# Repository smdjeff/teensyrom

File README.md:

# teensy rom

* Plugs directly into a 2716/512 socket
* Runs very fast firmware to emulate an 2716/512 EEPROM
* Loads rom.bin from SD card
* Polls CS pin to toggle data output or tristate
* Up to 64KB supported with jumpers to a board beyond the 2716 socket

## Dependencies
* https://www.adafruit.com/product/4622
* Arduino IDE
* Teensy 4.1
* Jumper wires
* $10 level shifting PCBA from JLCPCB (fabrication outputs included)

## Inspired
by Ted Fried, MicroCore Labs [ROM Emulator](https://github.com/MicroCoreLabs/Projects/tree/master/EPROM_Emulator)

2716             |  27512
:-------------------------:|:-------------------------:
  |

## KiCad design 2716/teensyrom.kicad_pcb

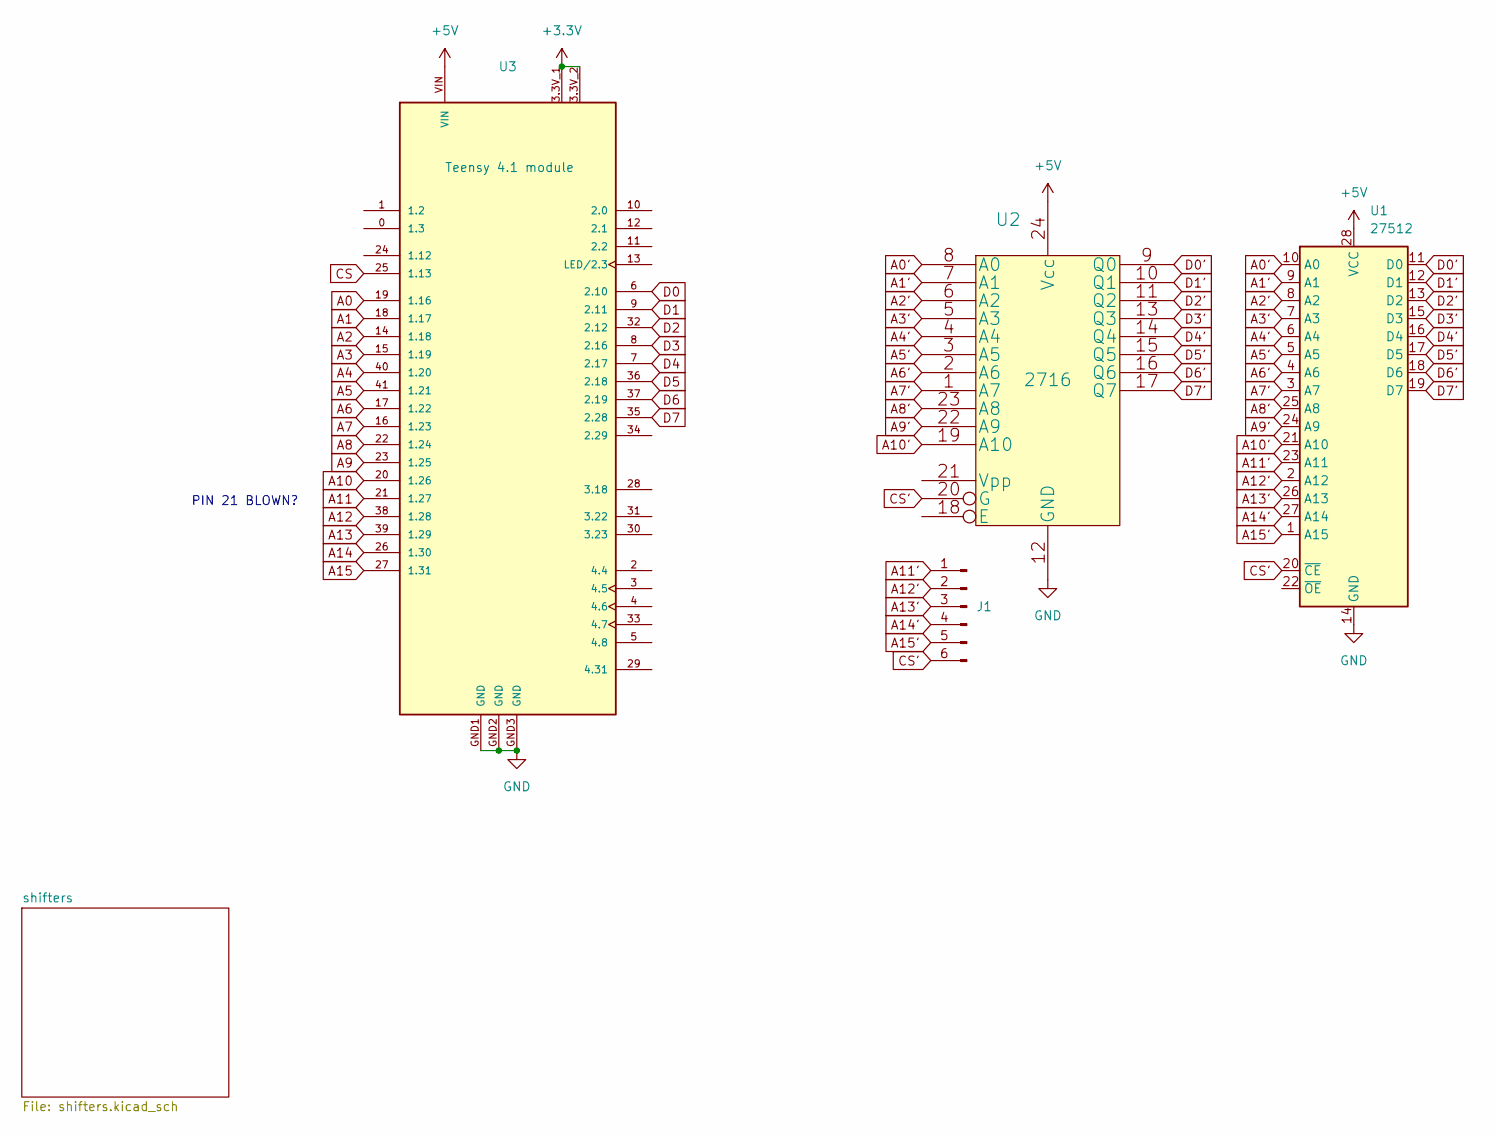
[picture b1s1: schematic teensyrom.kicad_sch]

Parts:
J1: Conn_01x06_Pin; PinHeader_1x06_P2.54mm_Vertical
U1: 27512; DIP-28_W15.24mm
U2: 2716; DIP-24_W15.24mm
U3: Teensy 4.1 module; MODULE_DEV-16771; PARTREV 4.1

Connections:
+3.3V: U3.3.3V_1, U3.3.3V_2; also elsewhere on the board
+5V: U1.28 (VCC), U2.24 (Vcc), U3.VIN; also elsewhere on the board
A0: U3.19 (1.16); also elsewhere on the board
A0': U1.10 (A0), U2.8 (A0); also elsewhere on the board
A1: U3.18 (1.17); also elsewhere on the board
A1': U1.9 (A1), U2.7 (A1); also elsewhere on the board
A2: U3.14 (1.18); also elsewhere on the board
A2': U1.8 (A2), U2.6 (A2); also elsewhere on the board
A3: U3.15 (1.19); also elsewhere on the board
A3': U1.7 (A3), U2.5 (A3); also elsewhere on the board
A4: U3.40 (1.20); also elsewhere on the board
A4': U1.6 (A4), U2.4 (A4); also elsewhere on the board
A5: U3.41 (1.21); also elsewhere on the board
A5': U1.5 (A5), U2.3 (A5); also elsewhere on the board
A6: U3.17 (1.22); also elsewhere on the board
A6': U1.4 (A6), U2.2 (A6); also elsewhere on the board
A7: U3.16 (1.23); also elsewhere on the board
A7': U1.3 (A7), U2.1 (A7); also elsewhere on the board
A8: U3.22 (1.24); also elsewhere on the board
A8': U1.25 (A8), U2.23 (A8); also elsewhere on the board
A9: U3.23 (1.25); also elsewhere on the board
A9': U1.24 (A9), U2.22 (A9); also elsewhere on the board
A10: U3.20 (1.26); also elsewhere on the board
A10': U1.21 (A10), U2.19 (A10); also elsewhere on the board
A11: U3.21 (1.27); also elsewhere on the board
A11': J1.1, U1.23 (A11); also elsewhere on the board
A12: U3.38 (1.28); also elsewhere on the board
A12': J1.2, U1.2 (A12); also elsewhere on the board
A13: U3.39 (1.29); also elsewhere on the board
A13': J1.3, U1.26 (A13); also elsewhere on the board
A14: U3.26 (1.30); also elsewhere on the board
A14': J1.4, U1.27 (A14); also elsewhere on the board
A15: U3.27 (1.31); also elsewhere on the board
A15': J1.5, U1.1 (A15); also elsewhere on the board
CS: U3.25 (1.13); also elsewhere on the board
CS': J1.6, U1.20 (~CE), U2.20 (G); also elsewhere on the board
D0: U3.6 (2.10); also elsewhere on the board
D0': U1.11 (D0), U2.9 (Q0); also elsewhere on the board
D1: U3.9 (2.11); also elsewhere on the board
D1': U1.12 (D1), U2.10 (Q1); also elsewhere on the board
D2: U3.32 (2.12); also elsewhere on the board
D2': U1.13 (D2), U2.11 (Q2); also elsewhere on the board
D3: U3.8 (2.16); also elsewhere on the board
D3': U1.15 (D3), U2.13 (Q3); also elsewhere on the board
D4: U3.7 (2.17); also elsewhere on the board
D4': U1.16 (D4), U2.14 (Q4); also elsewhere on the board
D5: U3.36 (2.18); also elsewhere on the board
D5': U1.17 (D5), U2.15 (Q5); also elsewhere on the board
D6: U3.37 (2.19); also elsewhere on the board
D6': U1.18 (D6), U2.16 (Q6); also elsewhere on the board
D7: U3.35 (2.28); also elsewhere on the board
D7': U1.19 (D7), U2.17 (Q7); also elsewhere on the board
GND: U1.14 (GND), U2.12 (GND), U3.GND1 (GND), U3.GND2 (GND), U3.GND3 (GND)

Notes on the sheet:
PIN 21 BLOWN?

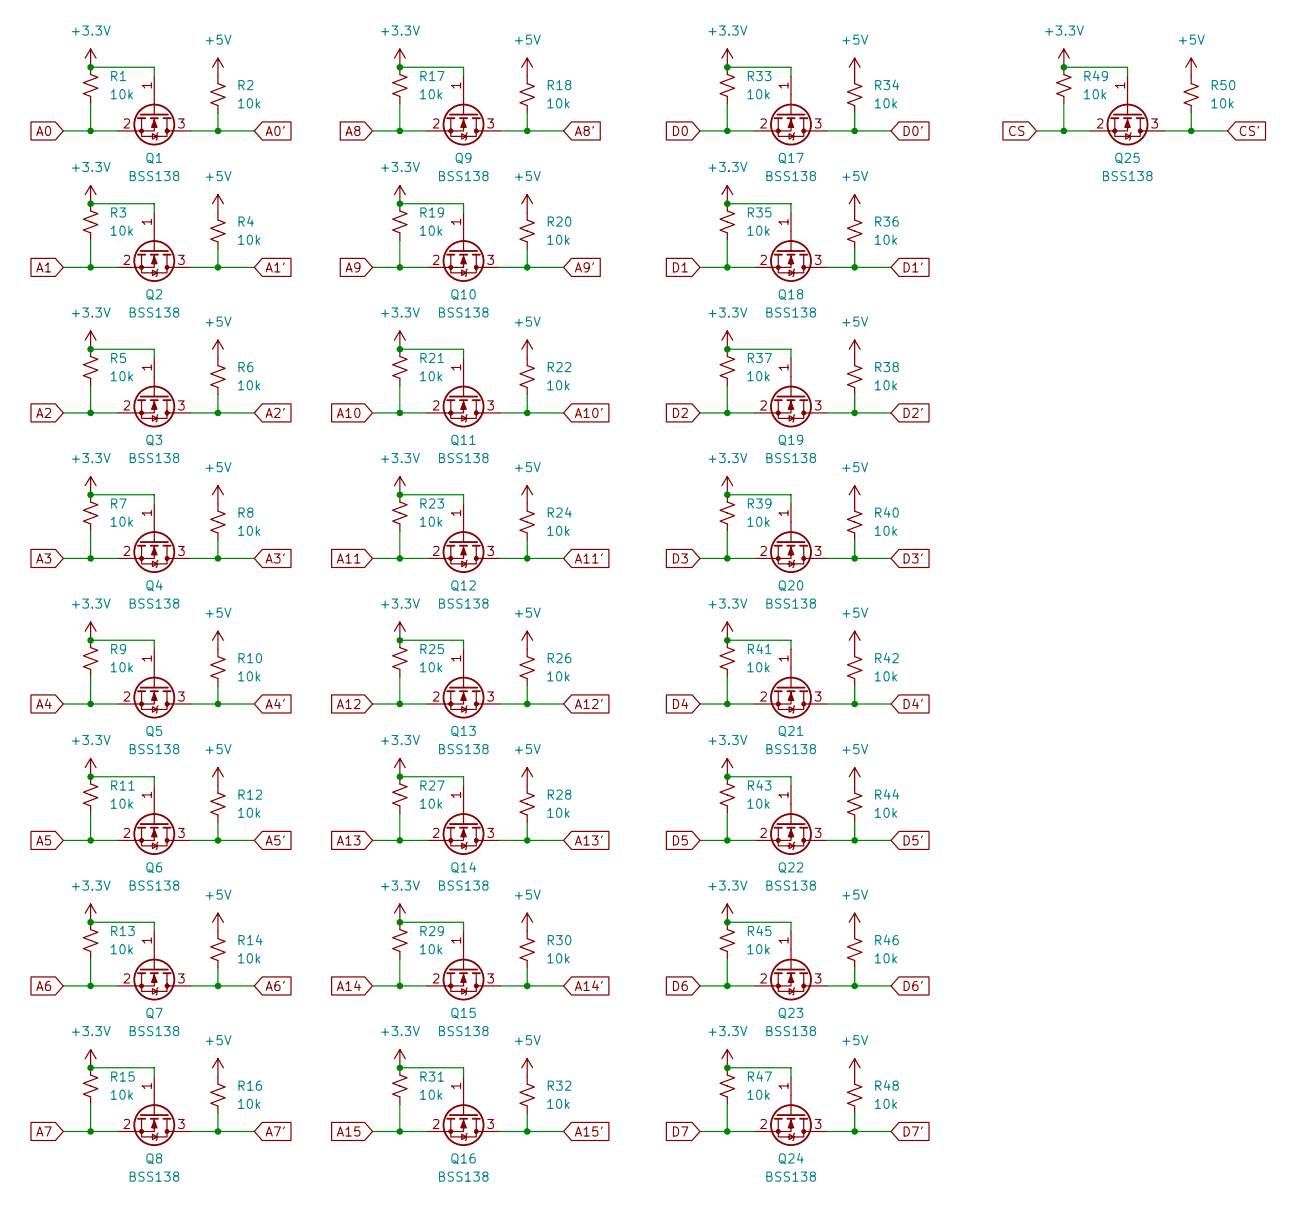
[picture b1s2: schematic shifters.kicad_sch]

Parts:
Q1, Q2, Q3, Q4, Q5, Q6, Q7, Q8, Q9, Q10, Q11, Q12, Q13, Q14, Q15, Q16, Q17, Q18, Q19, Q20, Q21, Q22, Q23, Q24, Q25: BSS138; SOT-23
R1, R2, R3, R4, R5, R6, R7, R8, R9, R10, R11, R12, R13, R14, R15, R16, R17, R18, R19, R20, R21, R22, R23, R24, R25, R26, R27, R28, R29, R30, R31, R32, R33, R34, R35, R36, R37, R38, R39, R40, R41, R42, R43, R44, R45, R46, R47, R48, R49, R50: 10k; R_0402_1005Metric

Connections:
+3.3V: Q1.1 (G), Q2.1 (G), Q3.1 (G), Q4.1 (G), Q5.1 (G), Q6.1 (G), Q7.1 (G), Q8.1 (G), Q9.1 (G), Q10.1 (G), Q11.1 (G), Q12.1 (G), Q13.1 (G), Q14.1 (G), Q15.1 (G), Q16.1 (G), Q17.1 (G), Q18.1 (G), Q19.1 (G), Q20.1 (G), Q21.1 (G), Q22.1 (G), Q23.1 (G), Q24.1 (G), Q25.1 (G), R1.1, R3.1, R5.1, R7.1, R9.1, R11.1, R13.1, R15.1, R17.1, R19.1, R21.1, R23.1, R25.1, R27.1, R29.1, R31.1, R33.1, R35.1, R37.1, R39.1, R41.1, R43.1, R45.1, R47.1, R49.1; also elsewhere on the board
+5V: R2.1, R4.1, R6.1, R8.1, R10.1, R12.1, R14.1, R16.1, R18.1, R20.1, R22.1, R24.1, R26.1, R28.1, R30.1, R32.1, R34.1, R36.1, R38.1, R40.1, R42.1, R44.1, R46.1, R48.1, R50.1; also elsewhere on the board
A0: Q1.2 (S), R1.2; also elsewhere on the board
A0': Q1.3 (D), R2.2; also elsewhere on the board
A1: Q2.2 (S), R3.2; also elsewhere on the board
A1': Q2.3 (D), R4.2; also elsewhere on the board
A2: Q3.2 (S), R5.2; also elsewhere on the board
A2': Q3.3 (D), R6.2; also elsewhere on the board
A3: Q4.2 (S), R7.2; also elsewhere on the board
A3': Q4.3 (D), R8.2; also elsewhere on the board
A4: Q5.2 (S), R9.2; also elsewhere on the board
A4': Q5.3 (D), R10.2; also elsewhere on the board
A5: Q6.2 (S), R11.2; also elsewhere on the board
A5': Q6.3 (D), R12.2; also elsewhere on the board
A6: Q7.2 (S), R13.2; also elsewhere on the board
A6': Q7.3 (D), R14.2; also elsewhere on the board
A7: Q8.2 (S), R15.2; also elsewhere on the board
A7': Q8.3 (D), R16.2; also elsewhere on the board
A8: Q9.2 (S), R17.2; also elsewhere on the board
A8': Q9.3 (D), R18.2; also elsewhere on the board
A9: Q10.2 (S), R19.2; also elsewhere on the board
A9': Q10.3 (D), R20.2; also elsewhere on the board
A10: Q11.2 (S), R21.2; also elsewhere on the board
A10': Q11.3 (D), R22.2; also elsewhere on the board
A11: Q12.2 (S), R23.2; also elsewhere on the board
A11': Q12.3 (D), R24.2; also elsewhere on the board
A12: Q13.2 (S), R25.2; also elsewhere on the board
A12': Q13.3 (D), R26.2; also elsewhere on the board
A13: Q14.2 (S), R27.2; also elsewhere on the board
A13': Q14.3 (D), R28.2; also elsewhere on the board
A14: Q15.2 (S), R29.2; also elsewhere on the board
A14': Q15.3 (D), R30.2; also elsewhere on the board
A15: Q16.2 (S), R31.2; also elsewhere on the board
A15': Q16.3 (D), R32.2; also elsewhere on the board
CS: Q25.2 (S), R49.2; also elsewhere on the board
CS': Q25.3 (D), R50.2; also elsewhere on the board
D0: Q17.2 (S), R33.2; also elsewhere on the board
D0': Q17.3 (D), R34.2; also elsewhere on the board
D1: Q18.2 (S), R35.2; also elsewhere on the board
D1': Q18.3 (D), R36.2; also elsewhere on the board
D2: Q19.2 (S), R37.2; also elsewhere on the board
D2': Q19.3 (D), R38.2; also elsewhere on the board
D3: Q20.2 (S), R39.2; also elsewhere on the board
D3': Q20.3 (D), R40.2; also elsewhere on the board
D4: Q21.2 (S), R41.2; also elsewhere on the board
D4': Q21.3 (D), R42.2; also elsewhere on the board
D5: Q22.2 (S), R43.2; also elsewhere on the board
D5': Q22.3 (D), R44.2; also elsewhere on the board
D6: Q23.2 (S), R45.2; also elsewhere on the board
D6': Q23.3 (D), R46.2; also elsewhere on the board
D7: Q24.2 (S), R47.2; also elsewhere on the board
D7': Q24.3 (D), R48.2; also elsewhere on the board

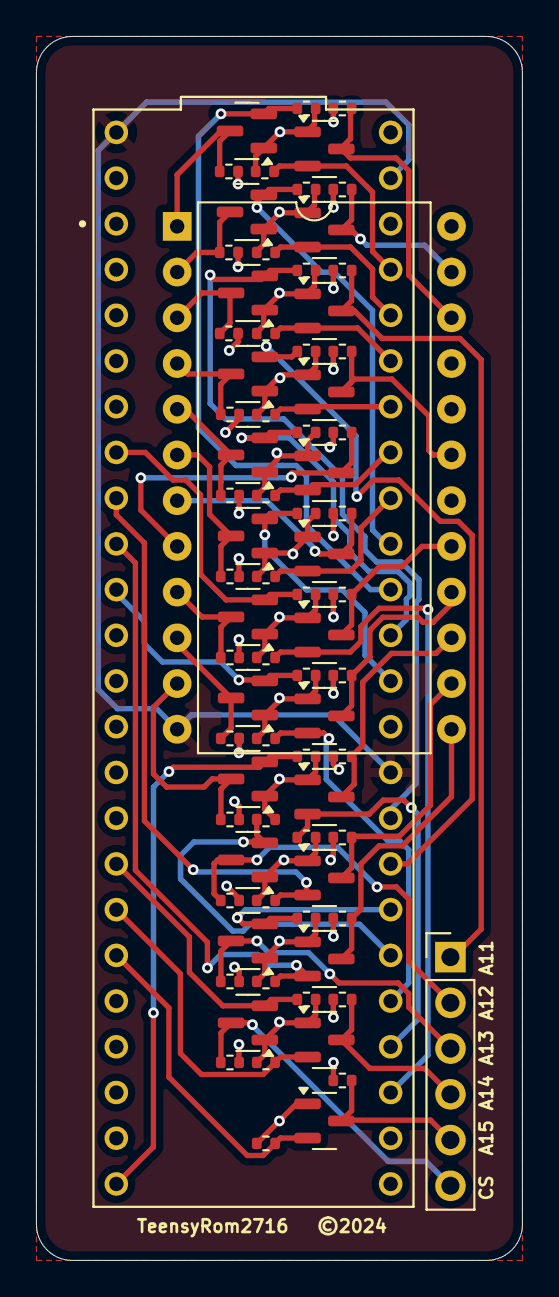
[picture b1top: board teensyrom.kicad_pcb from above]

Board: 4 copper layers, 27.0 x 68.0 mm, 78 parts (0 on the bottom side), 53 nets.

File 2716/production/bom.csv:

Designator,Footprint,Quantity,Value,LCSC Part #
"Q1, Q10, Q11, Q12, Q13, Q14, Q15, Q16, Q17, Q18, Q19, Q2, Q20, Q21, Q22, Q23, Q24, Q25, Q3, Q4, Q5, Q6, Q7, Q8, Q9",SOT-23,25,BSS138,
"R1, R10, R11, R12, R13, R14, R15, R16, R17, R18, R19, R2, R20, R21, R22, R23, R24, R25, R26, R27, R28, R29, R3, R30, R31, R32, R33, R34, R35, R36, R37, R38, R39, R4, R40, R41, R42, R43, R44, R45, R46, R47, R48, R49, R5, R50, R6, R7, R8, R9",0402,50,10k,
U2,DIP-24_W15.24mm,1,2716,
U3,MODULE_DEV-16771,1,Teensy 4.1 module,

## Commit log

2024-11-19 27512 version
2024-11-19 no message
2024-11-20 update schematic pdfs
2024-11-22 correct data output pins

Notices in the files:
2716/teensyrom.kicad_pcb:
TeensyRom2716 ©2024
